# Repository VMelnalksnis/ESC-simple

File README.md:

# ESC-simple

## Progress

### Software
1. Working "Blink" example for V1A
2. WIP "Control" example for V1A

### Hardware
* V1A is etched, partially soldered and tested with "Blink"
* V2A is WIP; planned changes:
	* Remove unnecessary pin connections
	* Change 7805 footprint to TO-220
	* Add 5V LED
	* Add 2 test LEDs
	* Add pull-down resistor to control input
	* Add mounting holes

### Documentation
Currently only in SOFTWARE in source.

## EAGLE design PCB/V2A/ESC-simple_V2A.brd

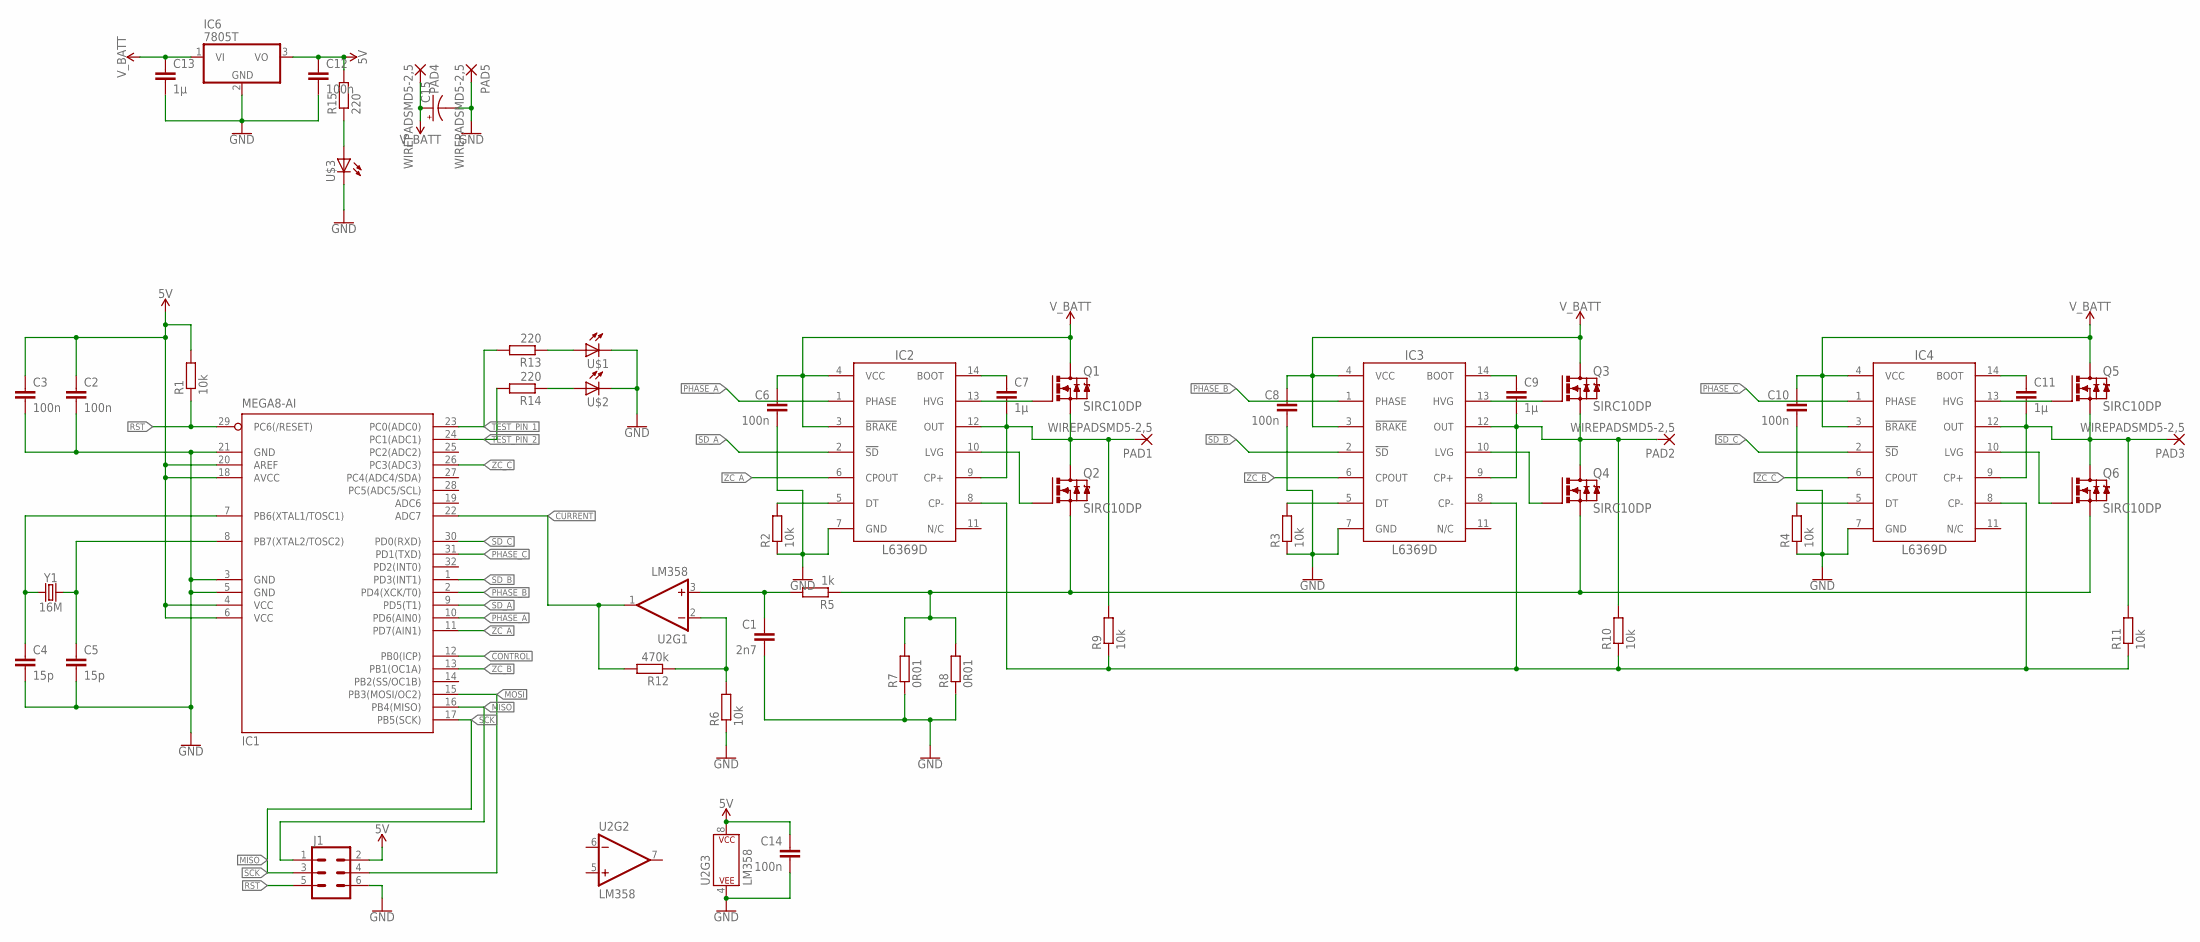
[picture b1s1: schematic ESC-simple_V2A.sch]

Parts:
C1: 2n7; C1206K
C2, C3, C6, C8, C10, C12, C14: 100n; C1206K
C4, C5: 15p; C1206K
C7, C9, C11, C13: 1µ; C1206K
C15: CPOL-USE5-13; E5-13
IC1: MEGA8-AI; TQFP32-08
IC2, IC3, IC4: L6369D; SO-14
IC6: 7805T; TO220H
J1: CONN_03X22X3_SILK_MALE_PTH; 2X3
PAD1, PAD2, PAD3, PAD4, PAD5: WIREPADSMD5-2,5; 5-2,5
Q1, Q2, Q3, Q4, Q5, Q6: SIRC10DP; POWERPAK_SO-8_SINGLE
R1, R2, R3, R4, R6, R9, R10, R11: 10k; R1206
R5: 1k; R1206
R7, R8: 0R01; R1206
R12: 470k; R1206
R13, R14, R15: 220; R1206
U2: LM358; DIP08
U$1, U$2, U$3: LED; 3MM_LED
Y1: 16M; HC49UP

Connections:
5V: C2.1, C3.1, C12.1, C14.1, IC1.4 (VCC), IC1.6 (VCC), IC1.18 (AVCC), IC1.20 (AREF), IC6.3 (VO), J1.2, R1.2, R15.2, U2.8 (P$V+)
A: C7.2, IC2.9 (CP+), IC2.12 (OUT), PAD1.1, Q1.1 (S), Q1.2 (S), Q1.3 (S), Q2.5 (D), Q2.6 (D), Q2.7 (D), Q2.8 (D), Q2.9 (D), R9.2
B: C9.2, IC3.9 (CP+), IC3.12 (OUT), PAD2.1, Q3.1 (S), Q3.2 (S), Q3.3 (S), Q4.5 (D), Q4.6 (D), Q4.7 (D), Q4.8 (D), Q4.9 (D), R10.2
C: C11.2, IC4.9 (CP+), IC4.12 (OUT), PAD3.1, Q5.1 (S), Q5.2 (S), Q5.3 (S), Q6.5 (D), Q6.6 (D), Q6.7 (D), Q6.8 (D), Q6.9 (D), R11.2
CONTROL: IC1.12 (PB0(ICP))
CURRENT: IC1.22 (ADC7), R12.2, U2.1 (OUT)
CURRENT_SENSE: Q2.1 (S), Q2.2 (S), Q2.3 (S), Q4.1 (S), Q4.2 (S), Q4.3 (S), Q6.1 (S), Q6.2 (S), Q6.3 (S), R5.1, R7.2, R8.2
GND: C1.2, C2.2, C3.2, C4.2, C5.2, C6.2, C8.2, C10.2, C12.2, C13.2, C14.2, C15.-, IC1.3 (GND), IC1.5 (GND), IC1.21 (GND), IC2.7 (GND), IC3.7 (GND), IC4.7 (GND), IC6.2 (GND), J1.6, PAD5.1, R2.1, R3.1, R4.1, R6.1, R7.1, R8.1, U2.4 (P$V-), U$1.C, U$2.C, U$3.C
MISO: IC1.16 (PB4(MISO)), J1.1
MOSI: IC1.15 (PB3(MOSI/OC2)), J1.4
unnamed: C7.1, IC2.14 (BOOT)
unnamed: IC2.13 (HVG), Q1.4 (G)
unnamed: IC2.10 (LVG), Q2.4 (G)
unnamed: IC3.5 (DT), R3.2
unnamed: IC2.5 (DT), R2.2
unnamed: C9.1, IC3.14 (BOOT)
unnamed: IC3.13 (HVG), Q3.4 (G)
unnamed: IC3.10 (LVG), Q4.4 (G)
unnamed: R6.2, R12.1, U2.2 (-IN)
unnamed: IC4.5 (DT), R4.2
unnamed: C11.1, IC4.14 (BOOT)
unnamed: IC4.13 (HVG), Q5.4 (G)
unnamed: IC4.10 (LVG), Q6.4 (G)
unnamed: R14.1, U$2.A
unnamed: R13.1, U$1.A
unnamed: R15.1, U$3.A
unnamed: C1.1, R5.2, U2.3 (+IN)
PHASE_A: IC1.10 (PD6(AIN0)), IC2.1 (PHASE)
PHASE_B: IC1.2 (PD4(XCK/T0)), IC3.1 (PHASE)
PHASE_C: IC1.31 (PD1(TXD)), IC4.1 (PHASE)
RST: IC1.29 (PC6(/RESET)), J1.5, R1.1
SCK: IC1.17 (PB5(SCK)), J1.3
SD_A: IC1.9 (PD5(T1)), IC2.2 (!SD)
SD_B: IC1.1 (PD3(INT1)), IC3.2 (!SD)
SD_C: IC1.30 (PD0(RXD)), IC4.2 (!SD)
TEST_PIN_1: IC1.23 (PC0(ADC0)), R13.2
TEST_PIN_2: IC1.24 (PC1(ADC1)), R14.2
V_BATT: C6.1, C8.1, C10.1, C13.1, C15.+, IC2.3 (!BRAKE), IC2.4 (VCC), IC3.3 (!BRAKE), IC3.4 (VCC), IC4.3 (!BRAKE), IC4.4 (VCC), IC6.1 (VI), PAD4.1, Q1.5 (D), Q1.6 (D), Q1.7 (D), Q1.8 (D), Q1.9 (D), Q3.5 (D), Q3.6 (D), Q3.7 (D), Q3.8 (D), Q3.9 (D), Q5.5 (D), Q5.6 (D), Q5.7 (D), Q5.8 (D), Q5.9 (D)
V_NEUTRAL: IC2.8 (CP-), IC3.8 (CP-), IC4.8 (CP-), R9.1, R10.1, R11.1
XTAL1: C4.1, IC1.7 (PB6(XTAL1/TOSC1)), Y1.1
XTAL2: C5.1, IC1.8 (PB7(XTAL2/TOSC2)), Y1.2
ZC_A: IC1.11 (PD7(AIN1)), IC2.6 (CPOUT)
ZC_B: IC1.13 (PB1(OC1A)), IC3.6 (CPOUT)
ZC_C: IC1.26 (PC3(ADC3)), IC4.6 (CPOUT)

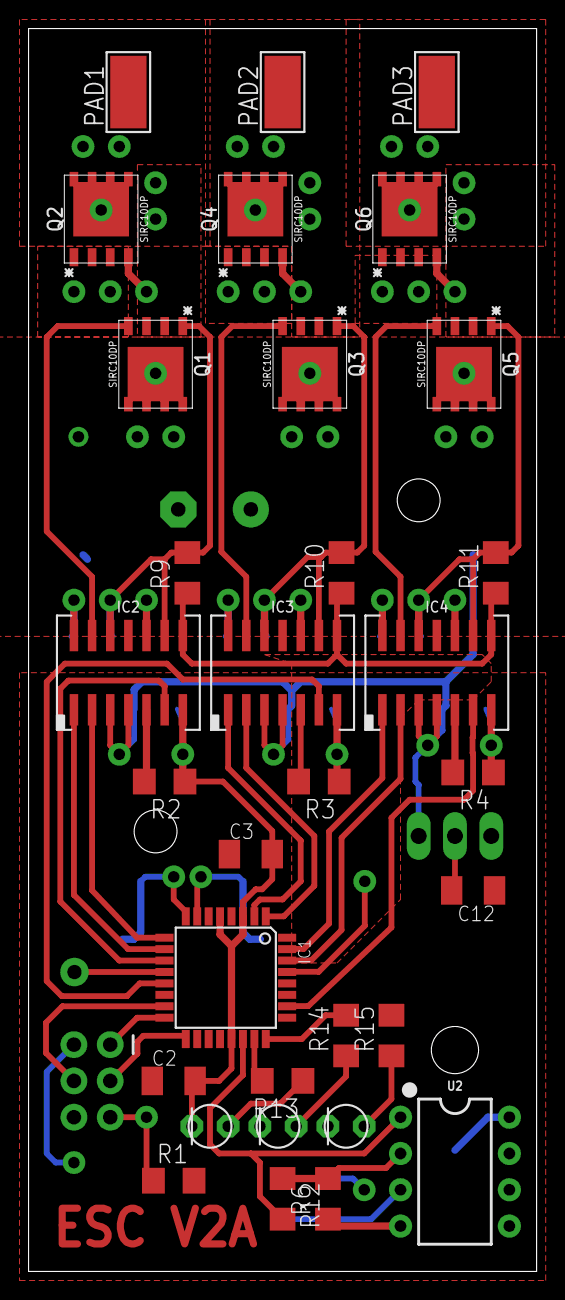
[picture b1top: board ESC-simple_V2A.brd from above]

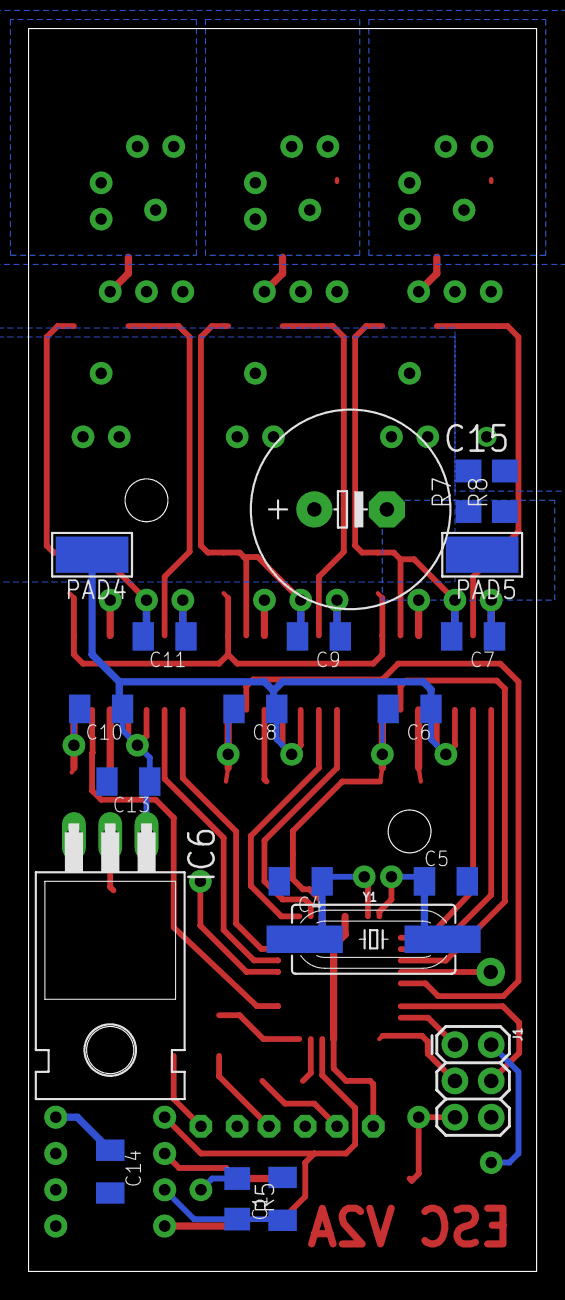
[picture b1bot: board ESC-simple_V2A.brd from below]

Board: 2 copper layers, 35.6 x 87.0 mm, 52 parts (20 on the bottom side), 43 nets.

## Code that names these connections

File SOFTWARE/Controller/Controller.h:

/*
 * Controller.h
 *
 * Created: 01.05.2018 15:47:08
 *  Author: Valters Melnalksnis
 */

/*	Pin map V2A
 *	12	PB0		ICP		IN	Control signal
 *	13	PB1		PCINT0	IN	Zero crossing Phase B (ZC_B)
 *	14	PB2		-		-	N/C
 *	15	PB3		MOSI	-	ISP
 *	16	PB4		MISO	-	ISP
 *	17	PB5		SCK		-	ISP
 *	7	PB6		XTAL1	-	Crystal
 *	8	PB7		XTAL2	-	Crystal
 *
 *	23	PC0		-		OUT	Test/status LED 1
 *	24	PC1		-		OUT	Test/status LED 2
 *	25	PC2		-		-	N/C
 *	26	PC3		PCINT11	IN	Zero crossing Phase C (ZC_C)
 *	27	PC4		-		-	N/C
 *	28	PC5		-		-	N/C
 *	29	PC6		RESET	-	ISP
 *
 *	30	PD0		-		OUT	Shutdown signal Phase C (SD_C)
 *	31	PD1		-		OUT	Phase signal Phase C (PHASE_C)
 *	32	PD2		-		-	N/C
 *	1	PD3		-		OUT	Shutdown signal Phase B (SD_B)
 *	2	PD4		-		OUT	Phase signal Phase B (PHASE_B)
 *	9	PD5		-		OUT Shutdown signal Phase A (SD_A)
 *	10	PD6		-		OUT	Phase signal Phase A (PHASE_A)
 *	11	PD7		PCINT23	IN	Zero crossing Phase A (ZC_A)
 *
 *	19	ADC6	-		-	N/C
 *	22	ADC7	ADC		IN	Current measurement
 */

#include <avr/io.h>
#include <avr/interrupt.h>

/*	Pins connected to LEDs used for testing and status indication.	*/
#define TEST_PIN_1		PINC0
#define TEST_PIN_2		PINC1
/*	DDR associated with the test/status pins.*/
#define TEST_DDR		DDRC
/*	PORT register associated with the test/status pins.	*/
#define TEST_PORT		PORTC

/*	Pins used to control the 3 half-bridge drivers.	*/
#define SD_C			PIND0
#define PHASE_C			PIND1
#define SD_B			PIND3
#define PHASE_B			PIND4
#define SD_A			PIND5
#define PHASE_A			PIND6
/*	DDR associated with the driver control pins.	*/
#define DRIVER_DDR		DDRD
/*	PORT register associated with the driver control pins.	*/
#define DRIVER_PORT		PORTD

/*	DRIVER_PORT states during each commutation state (ON).	*/
#define DRIVER_STATE_ON_1	((1 << SD_A) | (1 << PHASE_A) | (1 << SD_B))
#define DRIVER_STATE_ON_2	((1 << SD_A) | (1 << PHASE_A) | (1 << SD_C))
#define DRIVER_STATE_ON_3	((1 << SD_B) | (1 << PHASE_B) | (1 << SD_C))
#define DRIVER_STATE_ON_4	((1 << SD_B) | (1 << PHASE_B) | (1 << SD_A))
#define DRIVER_STATE_ON_5	((1 << SD_C) | (1 << PHASE_C) | (1 << SD_A))
#define DRIVER_STATE_ON_6	((1 << SD_C) | (1 << PHASE_C) | (1 << SD_B))

/*	DRIVER_PORT states during each commutation state (OFF).	*/
#define DRIVER_STATE_OFF_1	((1 << SD_A) | (1 << PHASE_A) | (1 << SD_B) | (1 << PHASE_B))
#define DRIVER_STATE_OFF_2	((1 << SD_A) | (1 << SD_C))
#define DRIVER_STATE_OFF_3	((1 << SD_B) | (1 << PHASE_B) | (1 << SD_C) | (1 << PHASE_C))
#define DRIVER_STATE_OFF_4	((1 << SD_B) | (1 << SD_A))
#define DRIVER_STATE_OFF_5	((1 << SD_C) | (1 << PHASE_C) | (1 << SD_A) | (1 << PHASE_A))
#define DRIVER_STATE_OFF_6	((1 << SD_C) | (1 << SD_B))

/*	Pin used to detect zero crossing for phase A. PCINT23.	*/
#define ZC_A_DDR		DDRD
#define ZC_A_PORT		PORTD
#define ZC_A_PINS		PIND
#define ZC_A_PIN		PIND7
#define ZC_A_INT		PCINT23

/*	Pin used to detect zero crossing for phase B. PCINT0.	*/
#define ZC_B_DDR		DDRB
#define ZC_B_PORT		PORTB
#define ZC_B_PINS		PINB
#define ZC_B_PIN		PINB0
#define ZC_B_INT		PCINT0

/*	Pin used to detect zero crossing for phase C. PCINT11.	*/
#define ZC_C_DDR		DDRC
#define ZC_C_PORT		PORTC
#define ZC_C_PINS		PINC
#define ZC_C_PIN		PINC3
#define ZC_C_INT		PCINT11

/*	Minimum control signal pulse width (1ms).	*/
#define CTRL_WIDTH_MIN	16000
/*	Maximum control signal pulse width (2ms).	*/
#define CTRL_WIDTH_MAX	32000

/*	Array containing driver commutation states in order.	*/
extern const uint8_t driver_states_on[6];
extern const uint8_t driver_states_off[6];

void InitIO(void);
void BlindStart(void);

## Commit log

2018-04-08 :circus_tent: Added .gitattributes
2018-04-08 Added .gitignore
2018-04-08 Added SOFTWARE/Blink
2018-04-08 Added PCB/V1A
2018-04-08 Added PCB/V2A
2018-04-08 Missed this
2018-04-08 Added SOFTWARE/Control
2018-04-09 Pre-test version of SOFTWARE/Control
2018-04-10 Updated SOFTWARE/Control
    The first version didn't work - it blinked randomly while a control signal was applied, and with a constant frequency when the control signal was removed.
    The program was restructured to run entirely in the ISR, and the startup check and timer1 overflow error was removed. More documentation was also added.
2018-04-11 Not working, waiting for PCB/V2A
    Planned to move control input to input capture pin PB0, in order to use input capture to time the pulse width.
2018-04-11 Initial SOFTWARE/Drivers commit
2018-04-12 Edited
2018-04-12 replaced paths
2018-04-20 Some changes
2018-04-20 V2A Final
    V2A already etched.
2018-04-20 V2A (#1)
    * Edited
    * replaced paths
    * V2A Final
    V2A already etched.
2018-04-27 Added docs, updated Blink for V2A
2018-04-28 Updated for testing purposes
2018-05-01 Updated EAGLE
2018-05-01 Working Input Capture
2018-05-01 Added input parsing
2018-05-10 Changes while testing

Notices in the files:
parts and their libraries:
SparkFun-Connectors: Licensing: Creative Commons ShareAlike 4.0 International - https://creativecommons.org/licenses/by-sa/4.0
